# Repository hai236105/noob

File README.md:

# noob
do sthing or die /n
find files in BRANCHES

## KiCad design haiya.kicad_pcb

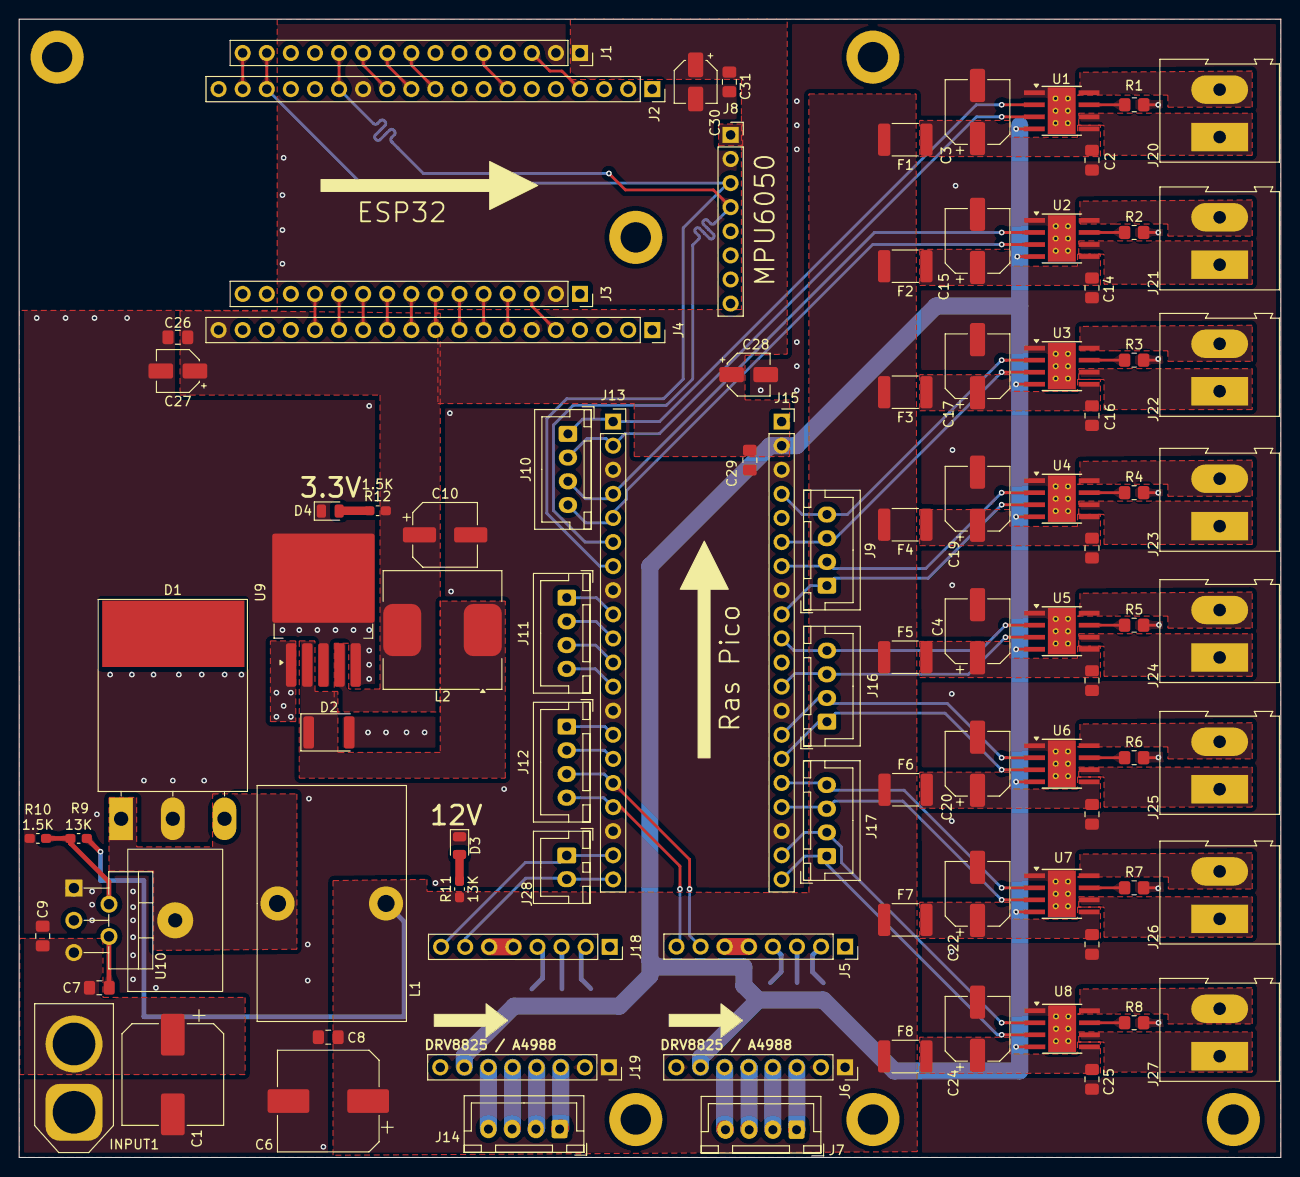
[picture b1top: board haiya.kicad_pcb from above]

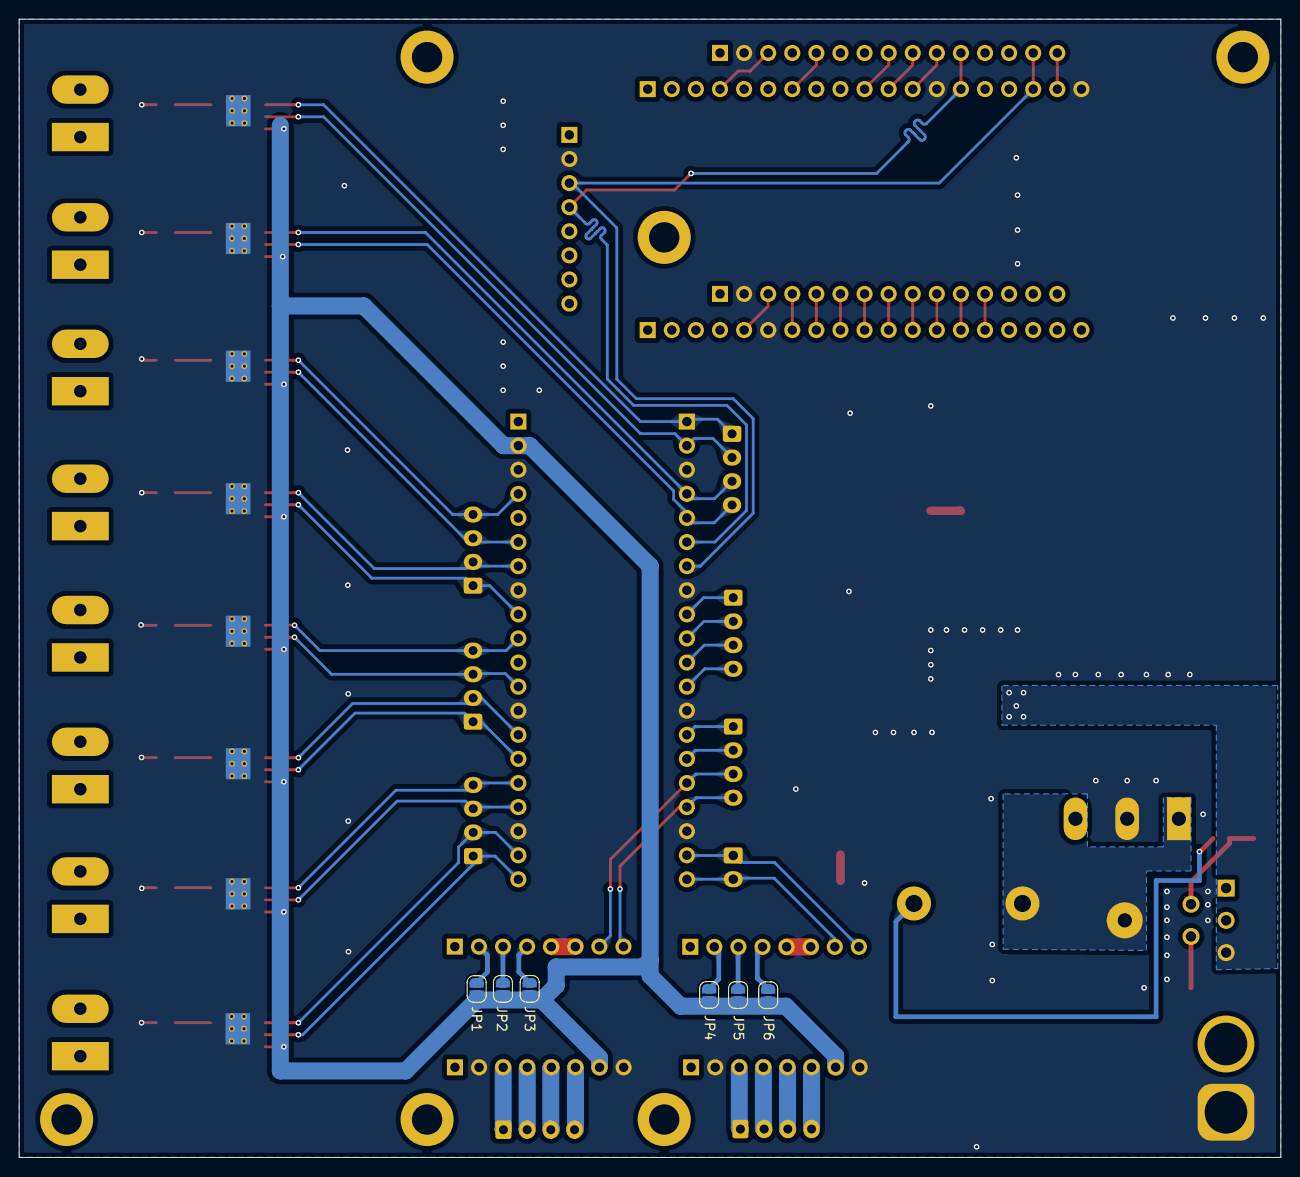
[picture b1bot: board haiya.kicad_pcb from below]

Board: 2 copper layers, 133.0 x 120.0 mm, 99 parts (6 on the bottom side), 102 nets.

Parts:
C1: SMD 470; CP_Elec_10x10.5
C2, C5, C14, C16, C18, C21, C23, C25, C26, C31: 0.1; C_0805_2012Metric_Pad1.18x1.45mm_HandSolder
C3, C4, C15, C17, C19, C20, C22, C24: 47; CP_Elec_6.3x5.4
C6: 470uF; CP_Elec_10x10.5
C7, C8, C9: 1uF; C_0805_2012Metric_Pad1.18x1.45mm_HandSolder
C10: 330; CP_Elec_6.3x7.7
C27, C30: 10; CP_Elec_4x5.4
C28: 10uF; CP_Elec_4x5.4
C29: 0.1uF; C_0805_2012Metric_Pad1.18x1.45mm_HandSolder
D1: MBR30100CT; TO-3P-3_Horizontal_TabDown
D2: SS34; D_1812_4532Metric
D3, D4: LED; LED_0805_2012Metric
F1, F2, F3, F4, F5, F6, F7, F8: Polyfuse; Fuse_1812_4532Metric_Pad1.30x3.40mm_HandSolder
INPUT1: Conn_01x02_Pin; AMASS_XT60-M_1x02_P7.20mm_Vertical
J1, J3: Conn_01x15; PinSocket_1x15_P2.54mm_Vertical
J2, J4: Conn_01x19; PinSocket_1x19_P2.54mm_Vertical
J5, J6, J18, J19: Conn_01x08; PinSocket_1x08_P2.54mm_Vertical
J7, J14: Conn_01x04; JST_XH_B4B-XH-A_1x04_P2.50mm_Vertical
J8: Conn_01x04; PinSocket_1x08_P2.54mm_Vertical
J9, J16, J17: M4; JST_XH_B4B-XH-A_1x04_P2.50mm_Vertical
J10: M1; JST_XH_B4B-XH-A_1x04_P2.50mm_Vertical
J11: M2; JST_XH_B4B-XH-A_1x04_P2.50mm_Vertical
J12: M3; JST_XH_B4B-XH-A_1x04_P2.50mm_Vertical
J13, J15: Conn_01x20; PinSocket_1x20_P2.54mm_Vertical
J20, J21, J22, J23, J24, J25, J26, J27: Conn_01x02_Pin; TerminalBlock_Altech_AK300-2_P5.00mm
J28: Conn_01x02; JST_XH_B2B-XH-A_1x02_P2.50mm_Vertical
JP1, JP2, JP3, JP4, JP5, JP6: SolderJumper_2_Open; SolderJumper-2_P1.3mm_Open_RoundedPad1.0x1.5mm
L1: 47 12A; L_Toroid_Vertical_L24.6mm_W15.5mm_P11.44mm_Pulse_KM-4
L2: 68 3A; L_Coilcraft_MSS1278-XXX
R1, R2, R3, R4, R5, R6, R7, R8: 0.2; R_0805_2012Metric_Pad1.20x1.40mm_HandSolder
R9, R11: 13K; C_0603_1608Metric_Pad1.08x0.95mm_HandSolder
R10, R12: 1.5K; C_0603_1608Metric_Pad1.08x0.95mm_HandSolder
U1, U2, U3, U4, U5, U6, U7, U8: DRV8870DDA; Texas_HTSOP-8-1EP_3.9x4.9mm_P1.27mm_EP2.95x4.9mm_Mask2.4x3.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
U9: LM2596S-3.3; TO-263-5_TabPin3
U10: XL4016; TO-220-5_P3.4x3.7mm_StaggerOdd_Lead3.8mm_Vertical

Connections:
+3.3V: C10.1, C26.1, C27.1, C28.1, C29.1, C30.1, C31.1, J1.1 (3v3), J4.19 (3V3), J6.7, J8.1, J15.2, J19.7, JP1.1 (A), JP2.1 (A), JP3.1 (A), JP4.1 (A), JP5.1 (A), JP6.1 (A), L2.2, R12.1, U1.4 (VREF), U2.4 (VREF), U3.4 (VREF), U4.4 (VREF), U5.4 (VREF), U6.4 (VREF), U7.4 (VREF), U8.4 (VREF), U9.4 (FB)
+12V: C6.1, C8.1, F1.2, F2.2, F3.2, F4.2, F5.1, F6.1, F7.1, F8.1, J6.1 (VIN), J19.1 (VIN), L1.2, R9.1, R11.1
+BATT: C1.1, C7.1, C9.1, INPUT1.2 (VCC), U9.1 (VIN), U10.5 (VIN)
-BATT: C1.2, C2.2, C3.2, C4.2, C5.2, C6.2, C8.2, C9.2, C10.2, C14.2, C15.2, C16.2, C17.2, C18.2, C19.2, C20.2, C21.2, C22.2, C23.2, C24.2, C25.2, C26.2, C27.2, C28.2, C29.2, C30.2, C31.2, D1.2 (A), D2.2 (A), D3.1 (K), D4.1 (K), INPUT1.1 (GND), J1.2 (GND), J2.13 (GND), J2.19 (GND), J3.2 (GND), J4.6 (GND), J6.2 (GND), J6.8, J8.2, J13.3, J13.8, J13.13, J13.18, J15.3, J15.8, J15.13, J15.18, J19.2 (GND), J19.8, R1.2, R2.2, R3.2, R4.2, R5.2, R6.2, R7.2, R8.2, R10.2, U1.1 (GND), U1.9 (GND), U2.1 (GND), U2.9 (GND), U3.1 (GND), U3.9 (GND), U4.1 (GND), U4.9 (GND), U5.1 (GND), U5.9 (GND), U6.1 (GND), U6.9 (GND), U7.1 (GND), U7.9 (GND), U8.1 (GND), U8.9 (GND), U9.3 (GND), U9.5 (~ON/OFF), U10.1 (GND)
/A4988 + MPU6050/DIR: J5.8 (DIR), J12.4, J13.17
/A4988 + MPU6050/DIR2: J13.19, J18.8 (DIR), J28.1
/A4988 + MPU6050/SCL: J1.14 (22), J2.17 (22), J8.3, J13.7
/A4988 + MPU6050/SDA: J1.11 (21), J2.14 (21), J8.4, J13.6
/A4988 + MPU6050/STEP: J5.7 (STEP), J12.3, J13.16
/A4988 + MPU6050/STEP2: J13.20, J18.7 (STEP), J28.2
/DRV/1.1: J10.2, J13.2, U1.3 (IN1)
/DRV/1.2: J10.1, J13.1, U1.2 (IN2)
/DRV/2.1: J10.4, J13.5, U2.3 (IN1)
/DRV/2.2: J10.3, J13.4, U2.2 (IN2)
/DRV/3.1: J9.3, J15.6, U3.3 (IN1)
/DRV/3.2: J9.4, J15.4, U3.2 (IN2)
/DRV/4.1: J9.1, J15.9, U4.3 (IN1)
/DRV/4.2: J9.2, J15.7, U4.2 (IN2)
/DRV/5.1: J15.12, J16.3, U5.3 (IN1)
/DRV/5.2: J15.10, J16.4, U5.2 (IN2)
/DRV/6.1: J15.15, J16.1, U6.3 (IN1)
/DRV/6.2: J15.14, J16.2, U6.2 (IN2)
/DRV/7.1: J15.17, J17.3, U7.3 (IN1)
/DRV/7.2: J15.16, J17.4, U7.2 (IN2)
/DRV/8.1: J15.20, J17.1, U8.3 (IN1)
/DRV/8.2: J15.19, J17.2, U8.2 (IN2)
/ESP32/4: J1.5 (4), J2.7 (4)
/ESP32/5: J1.8 (5), J2.10 (5)
/ESP32/12: J3.4 (12), J4.7 (12)
/ESP32/13: J3.3 (13), J4.5 (13)
/ESP32/14: J3.5 (14), J4.8 (14)
/ESP32/15: J1.3 (15), J2.4 (15)
/ESP32/18: J1.9 (18), J2.11 (18)
/ESP32/19: J1.10 (19), J2.12 (19)
/ESP32/23: J1.15 (23), J2.18 (23)
/ESP32/25: J3.8 (25), J4.11 (25)
/ESP32/26: J3.7 (26), J4.10 (26)
/ESP32/27: J3.6 (27), J4.9 (27)
/ESP32/32: J3.10 (32), J4.13 (32)
/ESP32/33: J3.9 (33), J4.12 (33)
/ESP32/34: J3.12 (34), J4.15 (34)
/ESP32/35: J3.11 (35), J4.14 (35)
/pico motor control/6: J11.1, J13.9
/pico motor control/7: J11.2, J13.10
/pico motor control/8: J11.3, J13.11
/pico motor control/9: J11.4, J13.12
/pico motor control/10: J12.1, J13.14
/pico motor control/11: J12.2, J13.15
unnamed: D1.1 (K), L1.1, U10.3 (SW)
unnamed: D2.1 (K), L2.1, U9.2 (OUT)
unnamed: D3.2 (A), R11.2
unnamed: D4.2 (A), R12.2
unnamed: J5.2 (MS1), JP1.2 (B)
unnamed: J5.3 (MS2), JP2.2 (B)
unnamed: J5.4 (MS3), JP3.2 (B)
unnamed: J5.5, J5.6
unnamed: J6.5 (1A), J7.3
unnamed: J6.6 (1B), J7.4
unnamed: J6.4 (2A), J7.2
unnamed: J6.3 (2B), J7.1
unnamed: J14.1, J19.3 (2B)
unnamed: J14.2, J19.4 (2A)
unnamed: J14.3, J19.5 (1A)
unnamed: J14.4, J19.6 (1B)
unnamed: J18.2 (MS1), JP4.2 (B)
unnamed: J18.3 (MS2), JP5.2 (B)
unnamed: J18.4 (MS3), JP6.2 (B)
unnamed: J18.5, J18.6
unnamed: J20.1, U1.6 (OUT1)
unnamed: J20.2, U1.8 (OUT2)
unnamed: J21.1, U2.6 (OUT1)
unnamed: J21.2, U2.8 (OUT2)
unnamed: J22.1, U3.6 (OUT1)
unnamed: J22.2, U3.8 (OUT2)
unnamed: J23.1, U4.6 (OUT1)
unnamed: J23.2, U4.8 (OUT2)
unnamed: J24.1, U5.6 (OUT1)
unnamed: J24.2, U5.8 (OUT2)
unnamed: J25.1, U6.6 (OUT1)
unnamed: J25.2, U6.8 (OUT2)
unnamed: J26.1, U7.6 (OUT1)
unnamed: J26.2, U7.8 (OUT2)
unnamed: J27.1, U8.6 (OUT1)
unnamed: J27.2, U8.8 (OUT2)
unnamed: R1.1, U1.7 (ISEN)
unnamed: C2.1, C3.1, F1.1, U1.5 (VM)
unnamed: R2.1, U2.7 (ISEN)
unnamed: C14.1, C15.1, F2.1, U2.5 (VM)
unnamed: R3.1, U3.7 (ISEN)
unnamed: C16.1, C17.1, F3.1, U3.5 (VM)
unnamed: R4.1, U4.7 (ISEN)
unnamed: C18.1, C19.1, F4.1, U4.5 (VM)
unnamed: R5.1, U5.7 (ISEN)
unnamed: C4.1, C5.1, F5.2, U5.5 (VM)
unnamed: R6.1, U6.7 (ISEN)
unnamed: C20.1, C21.1, F6.2, U6.5 (VM)
unnamed: R7.1, U7.7 (ISEN)
unnamed: C22.1, C23.1, F7.2, U7.5 (VM)
unnamed: R8.1, U8.7 (ISEN)
unnamed: C24.1, C25.1, F8.2, U8.5 (VM)
unnamed: R9.2, R10.1, U10.2 (FB)
unnamed: C7.2, U10.4 (VC)

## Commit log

2024-07-29 Create ddd
